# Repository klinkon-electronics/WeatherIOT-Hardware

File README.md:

# WeatherIOT-Hardware
Official repository about WeatherIOT Board and derivates (for example boards based on same hardware but with different layouts or sensors onboard)
Please contact Simone at klinkonelectronics@gmail.com or @Simoste1969 on telegram for asking mods or to upload new boards 

List of current boards:

WeatherIOT 0.3: Initial release of the board, implementing connectors for all kind of sensors, including sparkfun weather meter (anemometer and pluviometer), on board buck converter power supply (max 30V input) and ESD Protection

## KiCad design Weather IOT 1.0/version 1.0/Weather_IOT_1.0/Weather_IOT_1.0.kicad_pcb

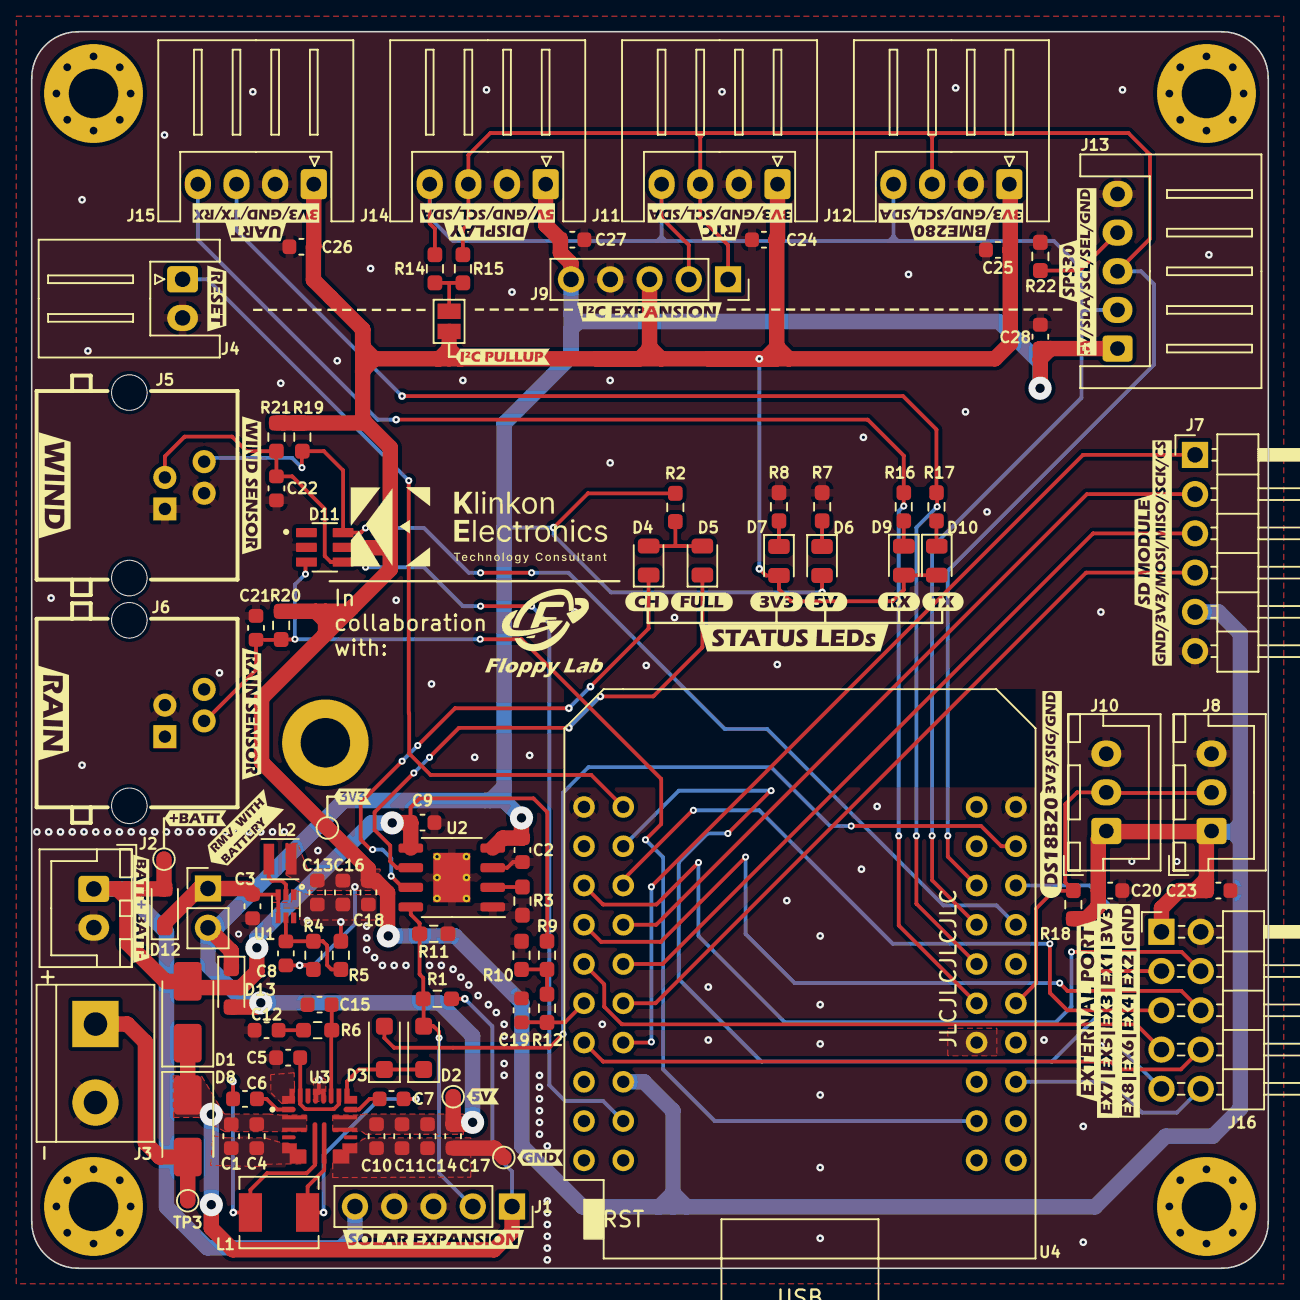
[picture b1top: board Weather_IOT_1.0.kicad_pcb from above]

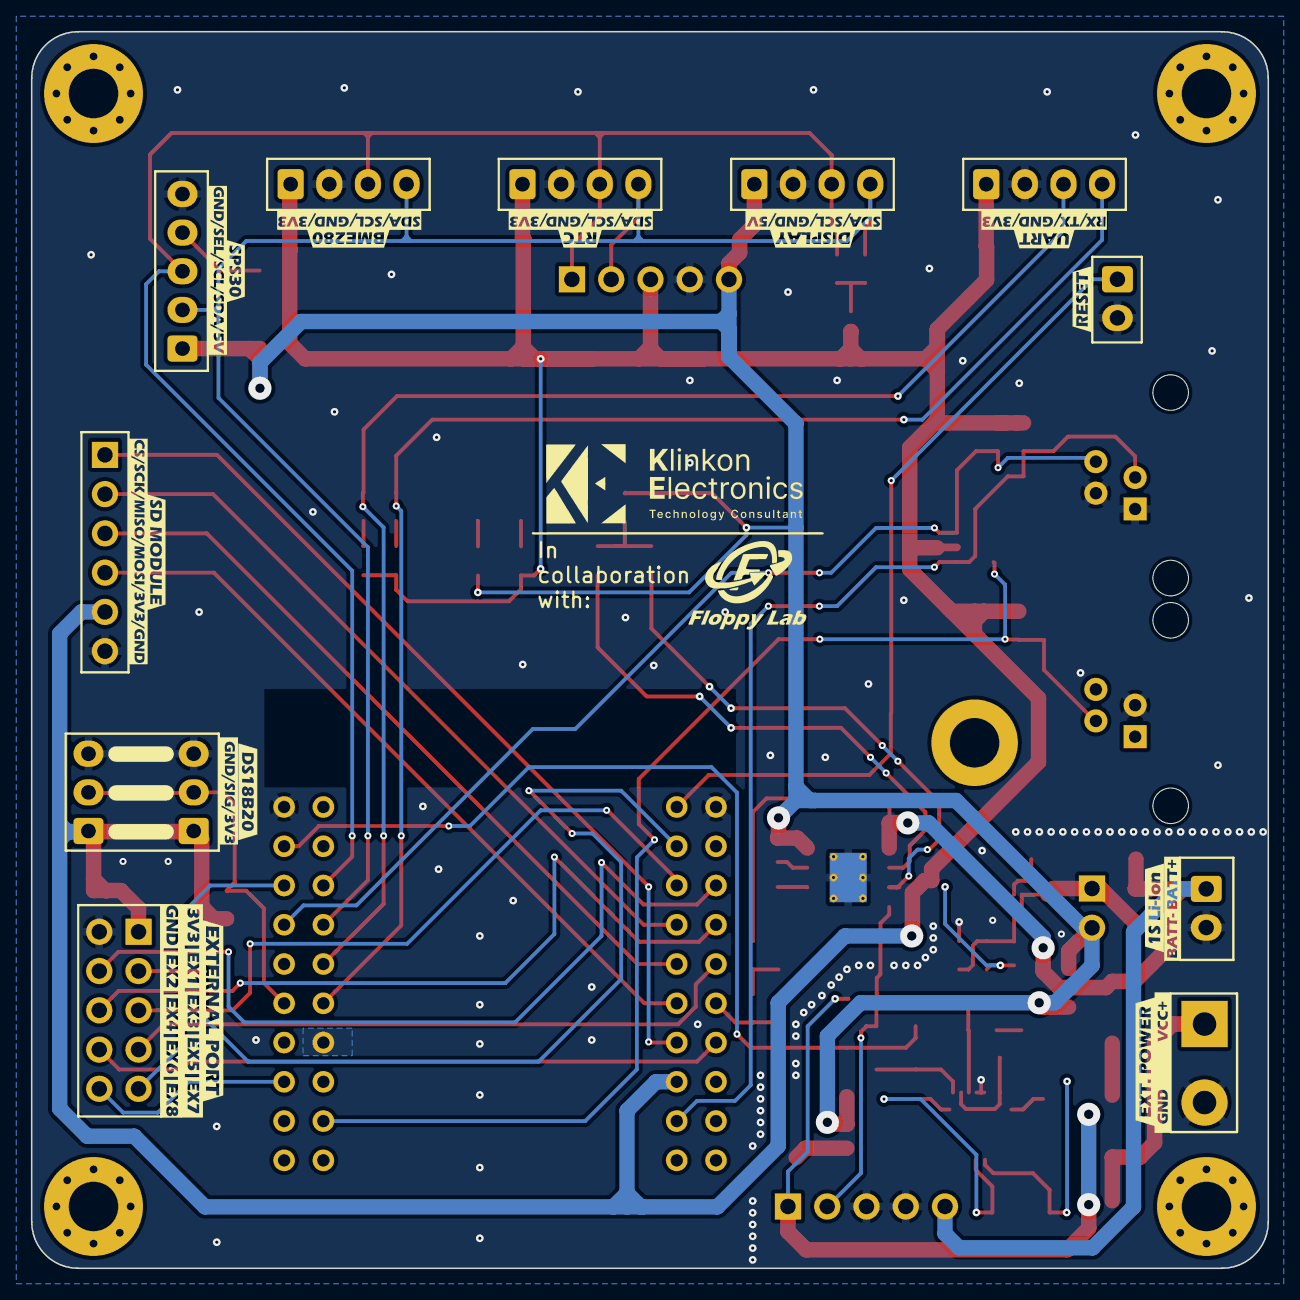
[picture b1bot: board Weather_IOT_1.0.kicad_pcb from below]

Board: 2 copper layers, 80.0 x 80.0 mm, 156 parts (22 on the bottom side), 52 nets.

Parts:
C1, C4, C5: 4.7u; C_0603_1608Metric
C2, C9, C13, C16, C18, C19: 10u; C_0603_1608Metric
C3, C10, C11, C14, C17: 22u; C_0603_1608Metric
C6, C7, C20, C23, C24, C25, C26, C27, C28: 100n; C_0603_1608Metric
C8: 120p; C_0603_1608Metric
C12: 22n; C_0603_1608Metric
C15: 100p; C_0603_1608Metric
C21, C22: 1uF; C_0603_1608Metric
D1, D8: SS34; D_SMA
D2, D3: SM4007PL; D_SOD-123F
D4: USB-CHRG; LED_0805_2012Metric
D5: USB-DONE; LED_0805_2012Metric
D6: PWR_5V; LED_0805_2012Metric
D7: PWR_3V3; LED_0805_2012Metric
D9: RX; LED_0805_2012Metric
D10: TX; LED_0805_2012Metric
D11: DT1042-04SO-7
D12, D13: CUS10S30; D_SOD-323_HandSoldering
H1, H2, H3, H4: MountingHole; MountingHole_3.2mm_M3_Pad_Via
H5: PV mount; MountingHole_3.2mm_M3_DIN965_Pad
J1: PV BOARD; PinSocket_1x05_P2.54mm_Vertical
J2: 1S Battery 1; JST_XH_B2B-XH-A_1x02_P2.50mm_Vertical
J3: Vin5-24V/12VFV; TerminalBlock_bornier-2_P5.08mm
J4: RESET; JST_XH_S2B-XH-A_1x02_P2.50mm_Horizontal
J5: Wind sense; R-RJ11R04P-A801
J6: Rain sense; R-RJ11R04P-A801
J7: SD_module; PinHeader_1x06_P2.54mm_Horizontal
J8, J10: DS18B20; JST_XH_B3B-XH-A_1x03_P2.50mm_Vertical
J9: to Expansion Board; PinSocket_1x05_P2.54mm_Vertical
J11: RTC; JST_XH_S4B-XH-A_1x04_P2.50mm_Horizontal
J12: BME280; JST_XH_S4B-XH-A_1x04_P2.50mm_Horizontal
J13: SPS30; JST_XH_S5B-XH-A_1x05_P2.50mm_Horizontal
J14: Display; JST_XH_S4B-XH-A_1x04_P2.50mm_Horizontal
J15: EXT_UART2; JST_XH_S4B-XH-A_1x04_P2.50mm_Horizontal
J16: EXPANSION_PORT; PinHeader_2x05_P2.54mm_Horizontal
JP1: Pullup_EN; SolderJumper-2_P1.3mm_Open_Pad1.0x1.5mm
JP2: no_BATT; PinHeader_1x02_P2.54mm_Vertical
L1: 2.2u; L_Chilisin_BMRA00040420
L2: 1uH; L_Taiyo-Yuden_NR-24xx
R1, R4: 100k; R_0603_1608Metric_Pad0.98x0.95mm_HandSolder
R2, R3, R7, R8, R12, R14, R15, R16, R17, R20, R21: 1k; R_0603_1608Metric_Pad0.98x0.95mm_HandSolder
R5: 22k; R_0603_1608Metric_Pad0.98x0.95mm_HandSolder
R6: 30k; R_0603_1608Metric_Pad0.98x0.95mm_HandSolder
R9, R10: 1M; R_0603_1608Metric_Pad0.98x0.95mm_HandSolder
R11: 33k; R_0603_1608Metric_Pad0.98x0.95mm_HandSolder
R18: 4.7k; R_0603_1608Metric_Pad0.98x0.95mm_HandSolder
R19, R22: 10k; R_0603_1608Metric_Pad0.98x0.95mm_HandSolder
TP1: 5V_tp; TestPoint_Pad_D1.0mm
TP2: 3V3_tp; TestPoint_Pad_D1.0mm
TP3: VCC_tp; TestPoint_Pad_D1.0mm
TP4: GND_tp; TestPoint_Pad_D1.0mm
TP5: VBATT_tp; TestPoint_Pad_D1.0mm
U1: TPS62A01A; SOT-563
U2: TP4056; HTSOP-8-1EP_3.9x4.9mm_P1.27mm_EP2.4x3.2mm_ThermalVias
U3: MAX25239AFFA_VY+
U4: Wemos_esp32_mini; ESP32_mini
kibuzzard-65C5F9F0: G***; kibuzzard-65C5F9F0
kibuzzard-65C5F9FB: G***; kibuzzard-65C5F9FB
kibuzzard-65C5F84F: G***; kibuzzard-65C5F84F
kibuzzard-65C5F840: G***; kibuzzard-65C5F840
kibuzzard-65C5FA29: G***; kibuzzard-65C5FA29
kibuzzard-65C5FA31: G***; kibuzzard-65C5FA31
kibuzzard-65C5FAB1, kibuzzard-65C5FAB1#2: G***; kibuzzard-65C5FAB1
kibuzzard-65C5FC57, kibuzzard-65C5FC57#2: G***; kibuzzard-65C5FC57
kibuzzard-65C5FCAF: G***; kibuzzard-65C5FCAF
kibuzzard-65C5FCBA: G***; kibuzzard-65C5FCBA
kibuzzard-65C5FCD1, kibuzzard-65C5FCD1#2: G***; kibuzzard-65C5FCD1
kibuzzard-65C5FCD9, kibuzzard-65C5FCD9#2: G***; kibuzzard-65C5FCD9
kibuzzard-65C5FCF3, kibuzzard-65C5FCF3#2: G***; kibuzzard-65C5FCF3
kibuzzard-65C5FD65, kibuzzard-65C5FD65#2: G***; kibuzzard-65C5FD65
kibuzzard-65C5FDCF: G***; kibuzzard-65C5FDCF
kibuzzard-65C5FDF5, kibuzzard-65C5FDF5#2: G***; kibuzzard-65C5FDF5
kibuzzard-65C5FE80: G***; kibuzzard-65C5FE80
kibuzzard-65C5FF49: G***; kibuzzard-65C5FF49
kibuzzard-65C5FF79: G***; kibuzzard-65C5FF79
kibuzzard-65C60A60: G***; kibuzzard-65C60A60
kibuzzard-65C60B28: G***; kibuzzard-65C60B28
kibuzzard-65C60C38: G***; kibuzzard-65C60C38
kibuzzard-65C60D2D: G***; kibuzzard-65C60D2D
kibuzzard-65C60D73: G***; kibuzzard-65C60D73
kibuzzard-65C60D82: G***; kibuzzard-65C60D82
kibuzzard-65C604B4: G***; kibuzzard-65C604B4
kibuzzard-65C604F6, kibuzzard-65C604F6#2: G***; kibuzzard-65C604F6
kibuzzard-65C608BF: G***; kibuzzard-65C608BF
kibuzzard-65C609AB, kibuzzard-65C609AB#2: G***; kibuzzard-65C609AB
kibuzzard-65C643D1: G***; kibuzzard-65C643D1
kibuzzard-65C643E1: G***; kibuzzard-65C643E1
kibuzzard-65C643FB: G***; kibuzzard-65C643FB
kibuzzard-65C643FF: G***; kibuzzard-65C643FF
kibuzzard-65C644A3: G***; kibuzzard-65C644A3
kibuzzard-65C644F8: G***; kibuzzard-65C644F8
kibuzzard-65C645B8: G***; kibuzzard-65C645B8
kibuzzard-65C648A6: G***; kibuzzard-65C648A6
kibuzzard-65C6048B: G***; kibuzzard-65C6048B
kibuzzard-65C6062C: G***; kibuzzard-65C6062C
kibuzzard-65C6116C: G***; kibuzzard-65C6116C
kibuzzard-65C6441A: G***; kibuzzard-65C6441A
kibuzzard-65C6444D: G***; kibuzzard-65C6444D
kibuzzard-65C60624: G***; kibuzzard-65C60624
kibuzzard-65C60828: G***; kibuzzard-65C60828
kibuzzard-65C60923: G***; kibuzzard-65C60923
kibuzzard-65C61177: G***; kibuzzard-65C61177
kibuzzard-65C64431: G***; kibuzzard-65C64431
kibuzzard-65C64477: G***; kibuzzard-65C64477
kibuzzard-65C64545: G***; kibuzzard-65C64545
kibuzzard-65C64592: G***; kibuzzard-65C64592
kibuzzard-65E8D7FD: G***; kibuzzard-65E8D7FD

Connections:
+3V3: C8.1, C13.1, C16.1, C18.1, C20.1, C23.1, C24.1, C25.1, C26.1, D7.2 (A), D9.2 (A), D10.2 (A), D11.5, J7.5, J8.1, J9.3, J10.1, J11.1, J12.1, J15.1, J16.1, JP1.2 (B), L2.2, R4.1, R18.1, R19.2, R20.2, R21.1, TP2.1, U4.16 (3V3)
+5V: C2.1, C10.1, C11.1, C14.1, C17.1, C27.1, C28.1, D6.2 (A), D13.2 (A), J9.5, J13.1, J14.1, JP2.2 (B), R2.2, TP1.1, U2.4 (VCC), U3.12 (OUT), U3.13 (OUT)
+BATT: C9.1, D1.2 (A), D12.2 (A), J1.5, J2.1, R9.1, TP5.1, U2.5 (BAT)
/MCU/5V_EN: D3.2 (A), U4.24 (IO_27)
/MCU/CS: J7.1, U4.14 (IO_05/D8)
/MCU/EXT_1: J16.3, U4.4 (IO_36/SVP/A0)
/MCU/EXT_2: J16.4, U4.5 (IO_39/SVN)
/MCU/EXT_3: J16.5, U4.6 (IO_26/D0)
/MCU/EXT_4: J16.6, U4.7 (IO_35)
/MCU/EXT_5: J16.7, U4.9 (IO_33)
/MCU/EXT_6: J16.8, U4.13 (IO_14/TMS)
/MCU/EXT_7: J16.9, U4.26 (IO_25)
/MCU/EXT_8: J16.10, U4.36 (IO_02)
/MCU/MISO: J7.3, U4.10 (IO_19/D6)
/MCU/MOSI: J7.4, U4.12 (IO_23/D7)
/MCU/RAIN: C21.2, D11.3, J6.2, R20.1, U4.37 (TD0)
/MCU/RESET: J4.1, U4.2 (RST)
/MCU/RX2: J15.4, R16.1, U4.31 (IO_16/D4)
/MCU/SCK: J7.2, U4.8 (IO_18/D5)
/MCU/TX2: J15.3, R17.1, U4.29 (IO_17/D3)
/MCU/VBAT_SENSE: C19.1, R12.2, U4.11 (IO_34)
/MCU/WIND_DIR: D11.6, J5.4, R19.1, U4.28 (IO_32)
/MCU/WIND_SPEED: C22.2, D11.4, J5.3, R21.2, U4.18 (IO_13/TCK)
/Power_circuit/BB_EN: D2.1 (K), D3.1 (K), U3.15 (EN)
/Power_circuit/BB_FB: C5.1, U3.16 (FB), U3.21 (VCC)
/Power_circuit/CHRG_C: D4.1 (K), U2.7 (~CHARG)
/Power_circuit/CHRG_D: D5.1 (K), U2.6 (~STDBY)
/Power_circuit/COMP: C15.1, R6.1, U3.17 (COMP)
/Power_circuit/FV_EN: D2.2 (A), J1.2, R1.1, R11.1, U2.8 (CE)
/Power_circuit/LX1: C6.1, L1.1, U3.7 (LX1)
/Power_circuit/LX2: C7.1, L1.2, U3.8 (LX2)
/Power_circuit/VCC_IN: D8.2 (A), J3.1, TP3.1
/Power_circuit/VIN_BUCK_3V3: C3.1, D12.1 (K), JP2.1 (A), U1.3 (VIN), U1.4 (EN)
/SCL: J9.1, J11.3, J12.3, J13.3, J14.3, R15.2, U4.25 (IO_22/D1/SCL)
/SDA: J9.2, J11.4, J12.4, J13.2, J14.4, R14.2, U4.27 (IO_21/D2/SDA)
/Sensors/DS18B20: J8.2, J10.2, R18.2, U4.32 (IO_04)
GND: C1.2, C2.2, C3.2, C4.2, C5.2, C9.2, C10.2, C11.2, C12.2, C13.2, C14.2, C15.2, C16.2, C17.2, C18.2, C19.2, C20.2, C21.1, C22.1, C23.2, C24.2, C25.2, C26.2, C27.2, C28.2, D11.2, J1.3, J1.4, J2.2, J3.2, J4.2, J5.1, J5.2, J6.3, J7.6, J8.3, J9.4, J10.3, J11.2, J12.2, J13.5, J14.2, J15.2, J16.2, R3.2, R5.2, R7.1, R8.1, R10.2, R11.2, R22.1, TP4.1, U1.1 (GND), U2.1 (TEMP), U2.3 (GND), U3.5_6 (PGND1), U3.9_10 (PGND2), U3.18 (SPS), U3.19 (SYNC), U3.22 (AGND), U4.1 (GND), U4.22 (GND), U4.33 (GND)
unnamed: C12.1, R6.2
unnamed: D4.2 (A), D5.2 (A), R2.1
unnamed: D6.1 (K), R7.2
unnamed: D7.1 (K), R8.2
unnamed: D9.1 (K), R16.2
unnamed: D10.1 (K), R17.2
unnamed: J13.4, R22.2
unnamed: JP1.1 (A), R14.1, R15.1
unnamed: R9.2, R10.1, R12.1
unnamed: C8.2, R4.2, R5.1, U1.5 (FB)
unnamed: L2.1, U1.2 (SW)
unnamed: R3.1, U2.2 (PROG)
unnamed: C6.2, U3.1 (BST1)
unnamed: C7.2, U3.14 (BST2)
VCC: C1.1, C4.1, D1.1 (K), D8.1 (K), J1.1, R1.2, U3.2 (SUP), U3.3 (SUP)

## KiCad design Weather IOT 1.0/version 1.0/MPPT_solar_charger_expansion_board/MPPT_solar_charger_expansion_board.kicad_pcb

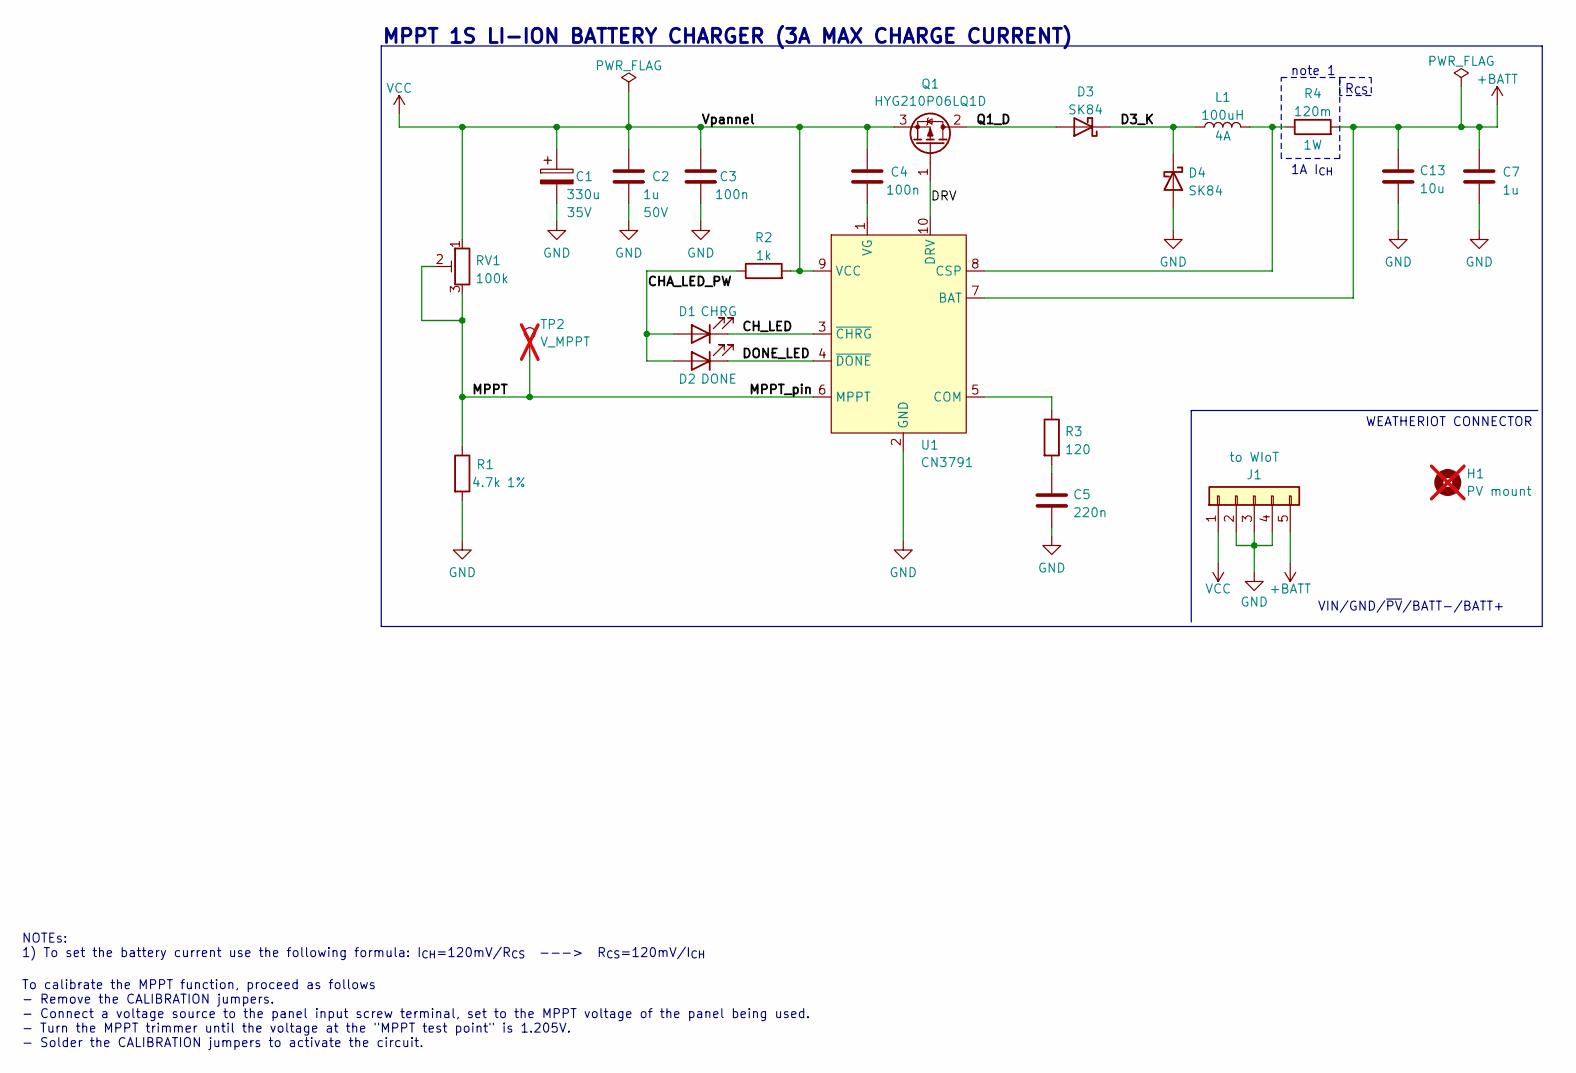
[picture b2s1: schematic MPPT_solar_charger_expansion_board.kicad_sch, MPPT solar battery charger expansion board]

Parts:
C1: 330u; CP_Radial_D8.0mm_P3.50mm; Voltage 35V; LCSC C357626
C2, C7: 1u; C_0603_1608Metric; Voltage 50V; LCSC C15849
C3, C4: 100n; C_0603_1608Metric; Voltage 50V; LCSC C282519
C5: 220n; C_0603_1608Metric; Voltage 50V; LCSC C64705
C13: 10u; C_0603_1608Metric; LCSC C96446
D1: CHRG; LED_0805_2012Metric; LCSC C965812
D2: DONE; LED_0805_2012Metric; LCSC C965815
D3, D4: SK84; D_SMB; LCSC C2922187
H1: PV mount; MountingHole_3.2mm_M3_ISO7380_Pad; not fitted
J1: to WIoT; PinHeader_1x05_P2.54mm_Vertical; LCSC C492404
L1: 100uH; L_TaiTech_TMPC1265_13.5x12.5mm; LCSC C357118
Q1: HYG210P06LQ1D; TO-252-2_TabPin1; LCSC C2834760
R1: 4.7k; R_0603_1608Metric; LCSC C2907034
R2: 1k; R_0603_1608Metric; LCSC C3016283
R3: 120; R_0603_1608Metric; LCSC C2906988
R4: 120m; R_2010_5025Metric; LCSC C3000625
RV1: 100k; Potentiometer_Bourns_3296W_Vertical; LCSC C48084
TP2: V_MPPT; TestPoint_THTPad_D1.5mm_Drill0.7mm; not fitted
U1: CN3791; SSOP-10_3.9x4.9mm_P1.00mm; LCSC C154992

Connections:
+BATT: C7.1, J1.5, R4.2, U1.7 (BAT); also elsewhere on the board
/CHA_LED_PW: D1.2 (A), D2.2 (A), R2.1
/CH_LED: D1.1 (K), U1.3 (~CHRG)
/D3_K: D3.1 (K), D4.1 (K), L1.1
/DONE_LED: D2.1 (K), U1.4 (~DONE)
/DRV: Q1.1 (G), U1.10 (DRV)
/MPPT: R1.1, RV1.2, RV1.3, TP2.1, U1.6 (MPPT)
/Q1_D: D3.2 (A), Q1.2 (D)
GND: C1.2, C2.2, C3.2, C5.2, C7.2, D4.2 (A), J1.2, J1.3, J1.4, R1.2, U1.2 (GND); also elsewhere on the board
unnamed: C5.1, R3.2
unnamed: R3.1, U1.5 (COM)
unnamed: L1.2, R4.1, U1.8 (CSP)
unnamed: C4.2, U1.1 (VG)
VCC: C1.1, C2.1, C3.1, C4.1, J1.1, Q1.3 (S), R2.2, RV1.1, U1.9 (VCC)

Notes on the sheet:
MPPT 1S LI-ION BATTERY CHARGER (3A MAX CHARGE CURRENT)
note 1
R_{CS}
To calibrate the MPPT function, proceed as follows - Remove the CALIBRATION jumpers. - Connect a voltage source to the panel input screw terminal, set to the MPPT voltage of the panel being used. - Turn the MPPT trimmer until the voltage at the "MPPT test point" is 1.205V. - Solder the CALIBRATION 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
VIN/GND/~{PV}/BATT-/BATT+
1A I_{CH}
WEATHERIOT CONNECTOR
NOTEs: 1) To set the battery current use the following formula: I_{CH}=120mV/R_{CS} ---> R_{CS}=120mV/I_{CH}

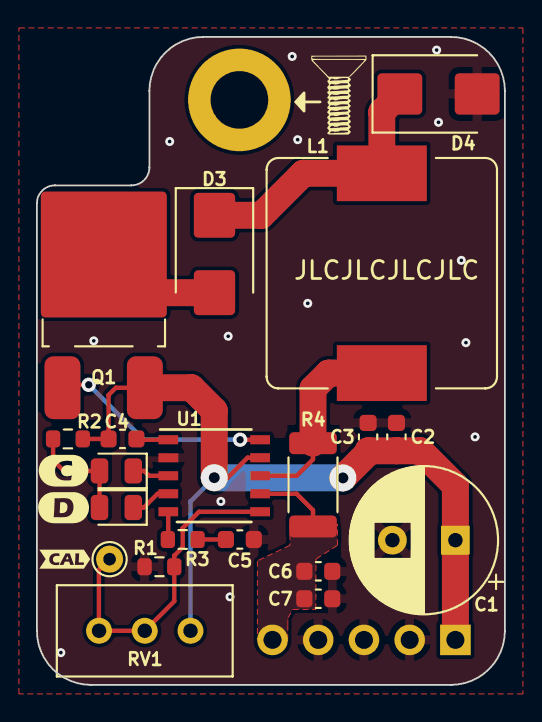
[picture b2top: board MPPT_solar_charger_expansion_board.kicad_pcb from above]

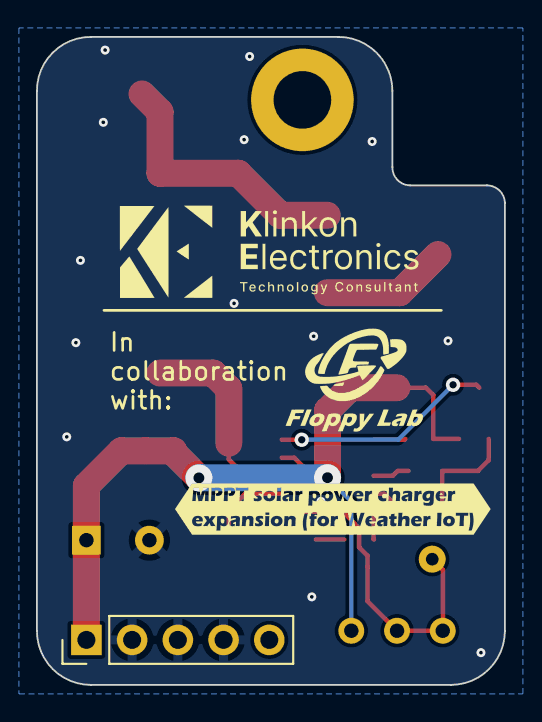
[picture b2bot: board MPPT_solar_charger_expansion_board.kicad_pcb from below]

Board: 2 copper layers, 26.0 x 36.0 mm, 26 parts (2 on the bottom side), 14 nets.

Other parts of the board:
C6: 10u; C_0603_1608Metric
kibuzzard-65C7DFB2: G***; kibuzzard-65C7DFB2
kibuzzard-65C7E01B: G***; kibuzzard-65C7E01B
kibuzzard-65C7E026: G***; kibuzzard-65C7E026
kibuzzard-65C8E163: G***; kibuzzard-65C8E163

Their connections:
+BATT: C6.1; also elsewhere on the board
GND: C6.2; also elsewhere on the board

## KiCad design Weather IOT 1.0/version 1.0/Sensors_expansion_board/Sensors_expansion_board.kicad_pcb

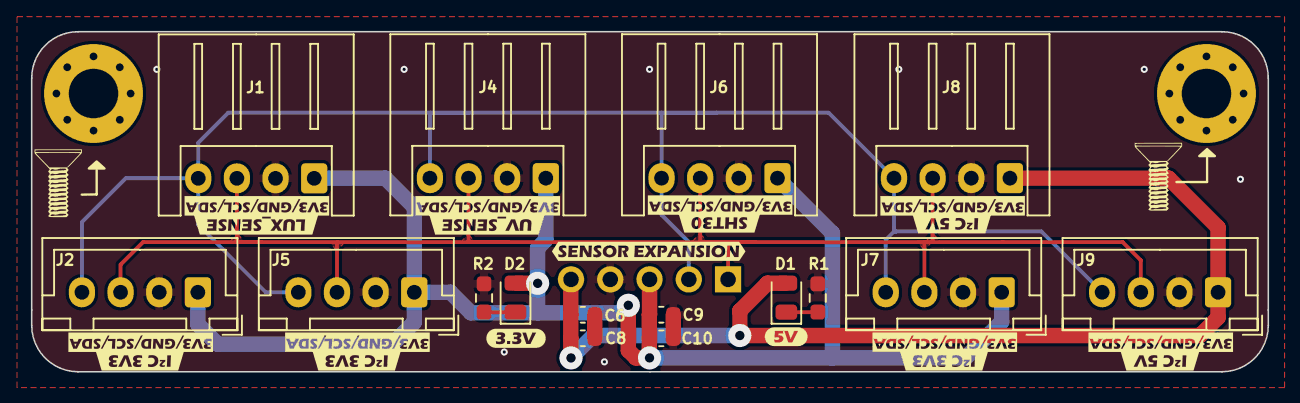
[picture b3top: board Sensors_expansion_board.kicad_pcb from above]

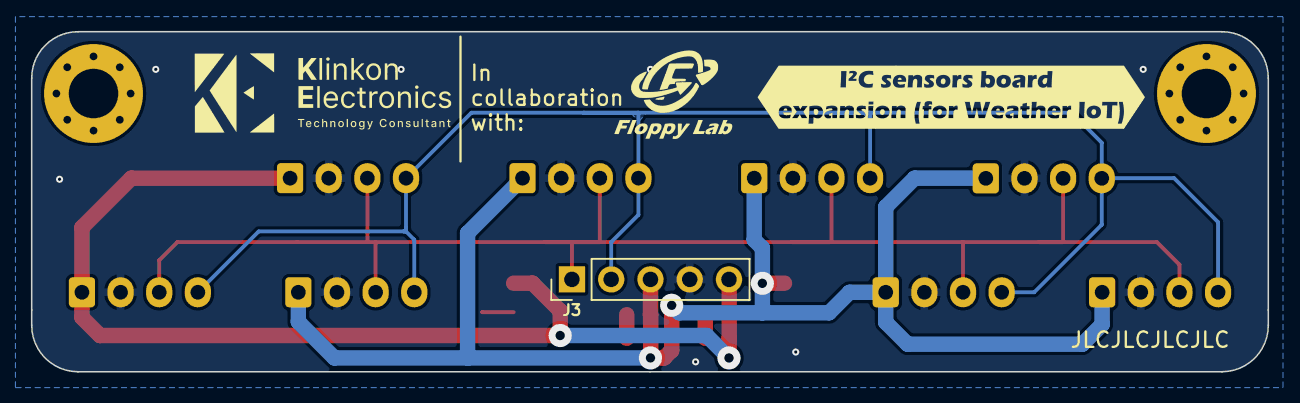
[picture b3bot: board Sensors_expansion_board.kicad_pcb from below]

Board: 2 copper layers, 80.0 x 22.0 mm, 39 parts (2 on the bottom side), 7 nets.

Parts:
C6, C9: 10u; C_0603_1608Metric
C8, C10: 100n; C_0603_1608Metric
D1: PWR_5V; LED_0805_2012Metric
D2: PWR_3V3; LED_0805_2012Metric
H1, H2: MountingHole; MountingHole_3.2mm_M3_Pad_Via
J1: LUX_Sensor; JST_XH_S4B-XH-A_1x04_P2.50mm_Horizontal
J2, J5, J7: I2C_3V3; JST_XH_B4B-XH-A_1x04_P2.50mm_Vertical
J3: to WIoT; PinHeader_1x05_P2.54mm_Vertical
J4: UV_Sensor; JST_XH_S4B-XH-A_1x04_P2.50mm_Horizontal
J6: SHT30 (soil); JST_XH_S4B-XH-A_1x04_P2.50mm_Horizontal
J8: I2C_5V; JST_XH_S4B-XH-A_1x04_P2.50mm_Horizontal
J9: I2C_5V; JST_XH_B4B-XH-A_1x04_P2.50mm_Vertical
R1, R2: 1k; R_0603_1608Metric_Pad0.98x0.95mm_HandSolder
kibuzzard-65C5FCD9, kibuzzard-65C5FCD9#2, kibuzzard-65C5FCD9#3, kibuzzard-65C5FCD9#4, kibuzzard-65C5FCD9#5, kibuzzard-65C5FCD9#6, kibuzzard-65C5FCD9#7, kibuzzard-65C5FCD9#8: G***; kibuzzard-65C5FCD9
kibuzzard-65C8D7CB: G***; kibuzzard-65C8D7CB
kibuzzard-65C8D7D6: G***; kibuzzard-65C8D7D6
kibuzzard-65C8D7E5: G***; kibuzzard-65C8D7E5
kibuzzard-65C8D72A, kibuzzard-65C8D72A#2, kibuzzard-65C8D72A#3: G***; kibuzzard-65C8D72A
kibuzzard-65C8D780, kibuzzard-65C8D780#2: G***; kibuzzard-65C8D780
kibuzzard-65C8D846: G***; kibuzzard-65C8D846
kibuzzard-65C8D862: G***; kibuzzard-65C8D862
kibuzzard-65C8E45A: G***; kibuzzard-65C8E45A
kibuzzard-65C8E424: G***; kibuzzard-65C8E424

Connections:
+3V3: C9.1, C10.1, D2.2 (A), J1.1, J2.1, J3.3, J4.1, J5.1, J6.1, J7.1
+5V: C6.1, C8.1, D1.2 (A), J3.5, J8.1, J9.1
/I2C_SCL: J1.3, J2.3, J3.1, J4.3, J5.3, J6.3, J7.3, J8.3, J9.3
/I2C_SDA: J1.4, J2.4, J3.2, J4.4, J5.4, J6.4, J7.4, J8.4, J9.4
GND: C6.2, C8.2, C9.2, C10.2, J1.2, J2.2, J3.4, J4.2, J5.2, J6.2, J7.2, J8.2, J9.2, R1.1, R2.1
unnamed: D1.1 (K), R1.2
unnamed: D2.1 (K), R2.2

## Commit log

2024-10-06 First commit WIoT 1.0 project
